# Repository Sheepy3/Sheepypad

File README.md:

# Sheepypad
open source Macropad for art, gaming... whatever you want, man.

## ok but what is it 
this is a repo containing a fairly rudimentary macropad schematic and accompanying circuitpython code. 

the supplied macropad contains:
- 1x mode switching tactile switch
- 2x rotary encoders
- 1x 5-way switch
- 9x mechanical keyswitches
- 1x 128x32 SSD1306 OLED
- 1x Rasberry Pi Pico (or other pin-out compatible rp2040 board) 

I have written firmware to make it fairly simple to create and modify profiles for this pad. 
I intend to use it with art programs and flight sim.

## why was this made
I wanted to dip my toes into circuit design with a project I felt I could actually benefit from. this was the result. 
if you've ever wanted a super basic example project for making a HID device in circuitpython, this may be useful to you too!

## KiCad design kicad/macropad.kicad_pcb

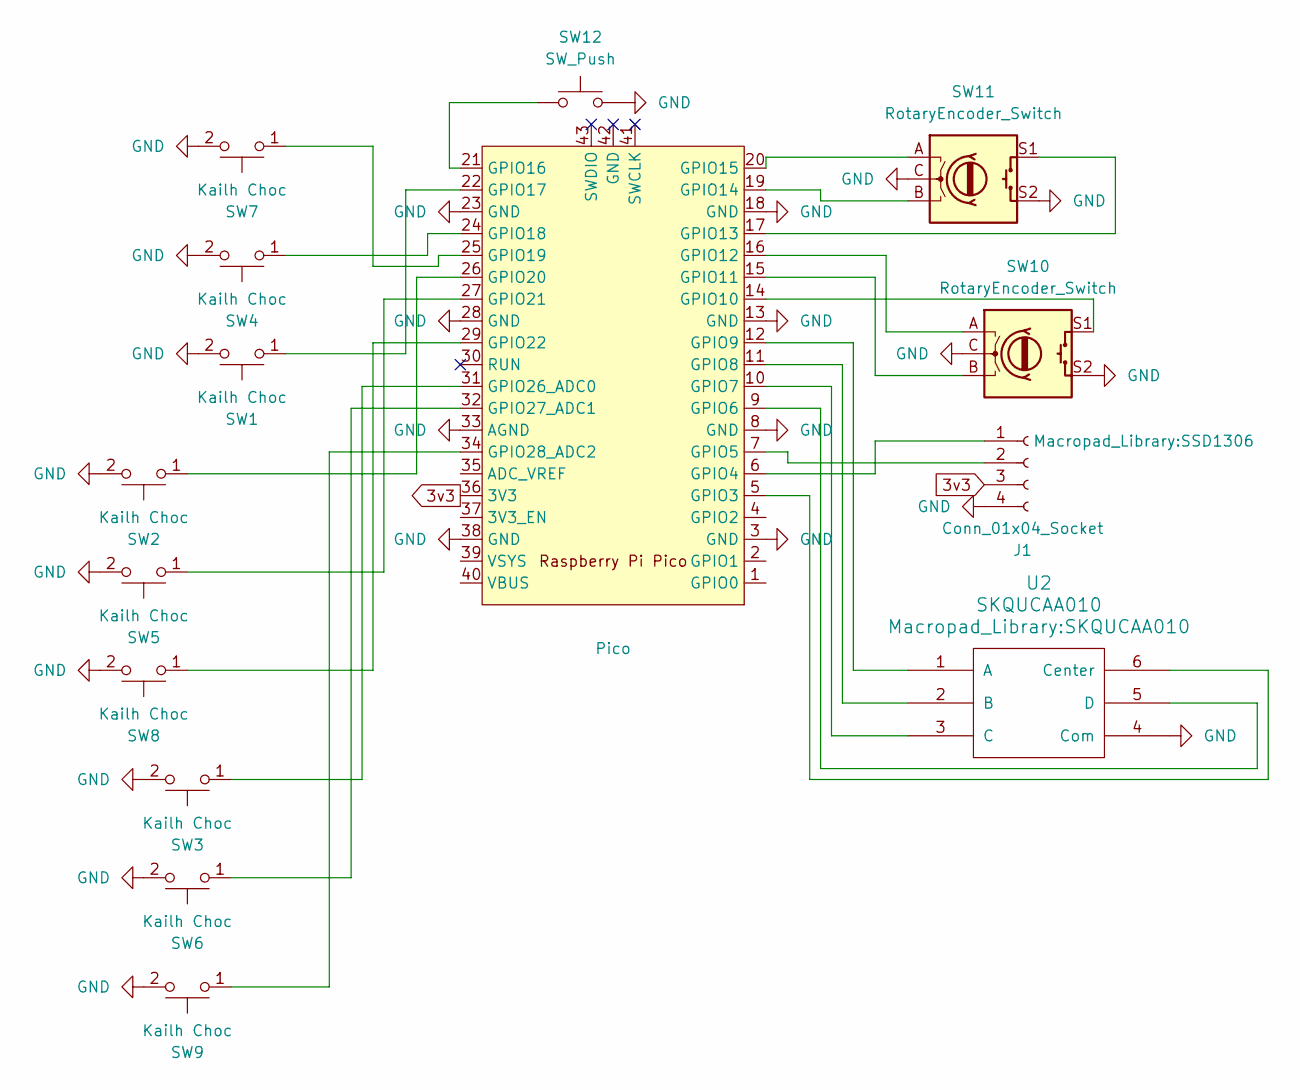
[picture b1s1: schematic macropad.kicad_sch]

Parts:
J1: Conn_01x04_Socket; SSD1306
SW1, SW2, SW3, SW4, SW5, SW6, SW7, SW8, SW9: Kailh Choc; SW_PG1350
SW10, SW11: RotaryEncoder_Switch; RotaryEncoder
SW12: SW_Push; SW_PUSH-12mm
U1: Pico; RPi_Pico_SMD_TH
U2: SKQUCAA010

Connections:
3v3: J1.3, U1.36 (3V3)
GND: J1.4, SW1.2, SW2.2, SW3.2, SW4.2, SW5.2, SW6.2, SW7.2, SW8.2, SW9.2, SW10.C, SW10.S2, SW11.C, SW11.S2, SW12.2, U1.3 (GND), U1.8 (GND), U1.13 (GND), U1.18 (GND), U1.23 (GND), U1.28 (GND), U1.33 (AGND), U1.38 (GND), U2.4 (Com)
unnamed: J1.1, U1.6 (GPIO4)
unnamed: J1.2, U1.7 (GPIO5)
unnamed: U1.5 (GPIO3), U2.6 (Center)
unnamed: U1.9 (GPIO6), U2.5 (D)
unnamed: U1.10 (GPIO7), U2.3 (C)
unnamed: U1.11 (GPIO8), U2.2 (B)
unnamed: U1.12 (GPIO9), U2.1 (A)
unnamed: SW10.S1, U1.14 (GPIO10)
unnamed: SW10.B, U1.15 (GPIO11)
unnamed: SW10.A, U1.16 (GPIO12)
unnamed: SW11.S1, U1.17 (GPIO13)
unnamed: SW11.B, U1.19 (GPIO14)
unnamed: SW11.A, U1.20 (GPIO15)
unnamed: SW12.1, U1.21 (GPIO16)
unnamed: SW1.1, U1.22 (GPIO17)
unnamed: SW4.1, U1.24 (GPIO18)
unnamed: SW7.1, U1.25 (GPIO19)
unnamed: SW2.1, U1.26 (GPIO20)
unnamed: SW5.1, U1.27 (GPIO21)
unnamed: SW8.1, U1.29 (GPIO22)
unnamed: SW3.1, U1.31 (GPIO26_ADC0)
unnamed: SW6.1, U1.32 (GPIO27_ADC1)
unnamed: SW9.1, U1.34 (GPIO28_ADC2)

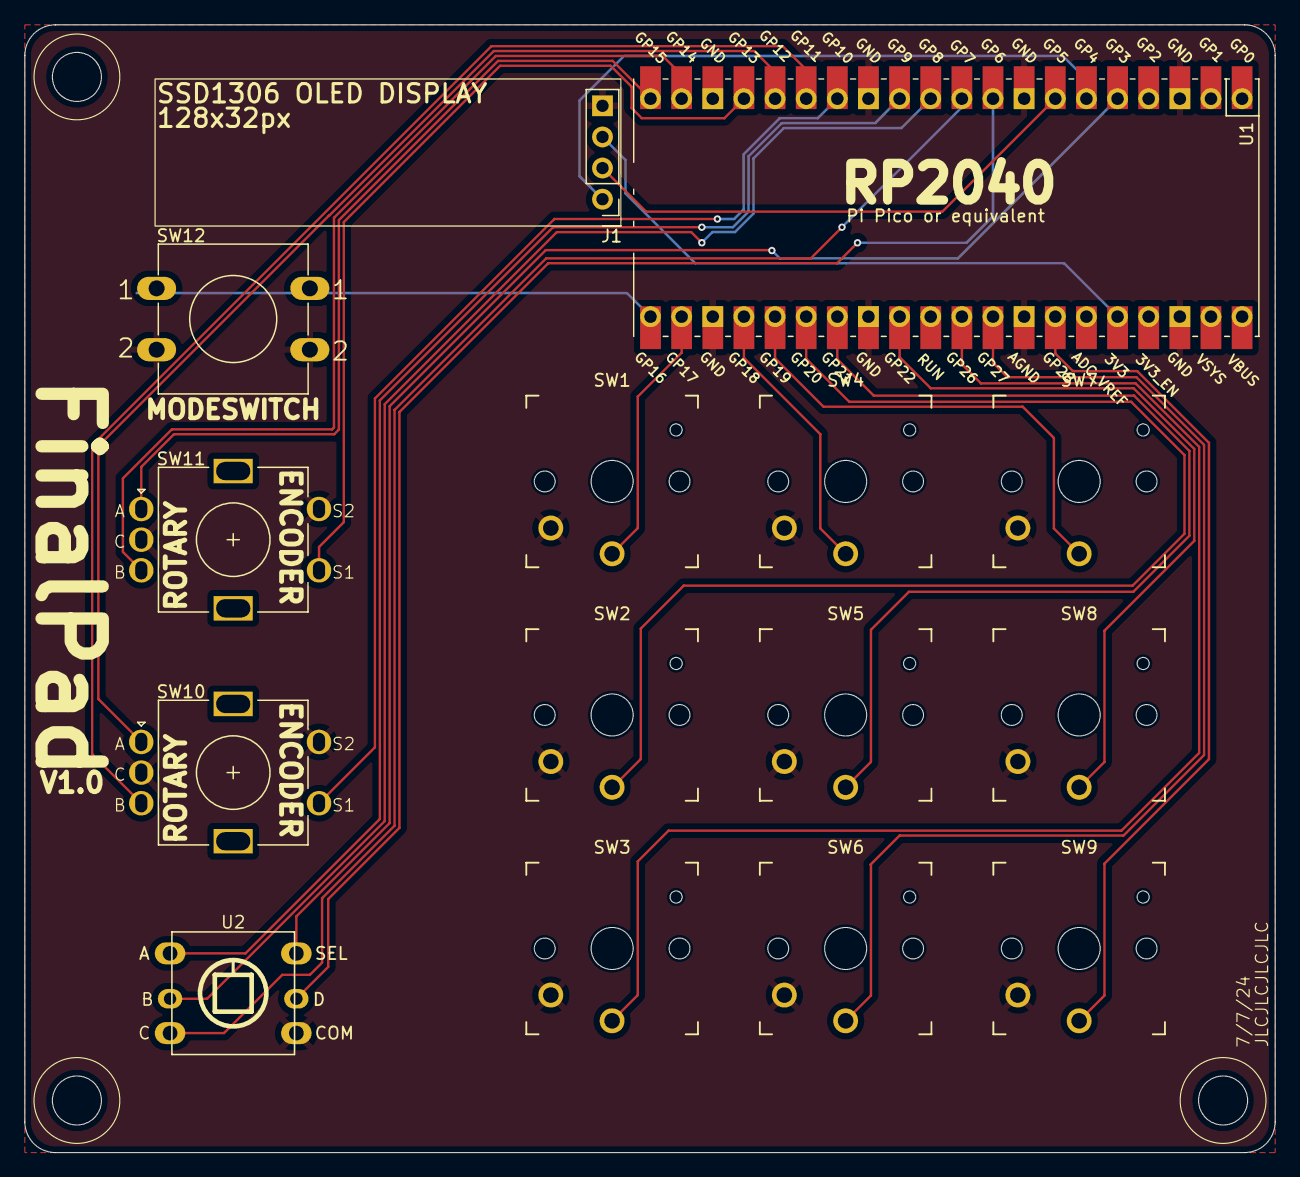
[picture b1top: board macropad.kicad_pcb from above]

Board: 2 copper layers, 102.0 x 92.0 mm, 15 parts (0 on the bottom side), 25 nets.

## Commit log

2024-05-09 added kicad and circuitpython
2024-07-06 updated design
2024-07-07 added 3D models
2024-07-07 updated silkscreen and moved switches up
2024-07-07 Delete kicad/macropad-backups directory
    unneeded in repo
2024-07-07 updated library
2024-07-24 new gerbers
2025-01-02 gerbers + boot script
2025-01-02 fixed the profile switch crash
